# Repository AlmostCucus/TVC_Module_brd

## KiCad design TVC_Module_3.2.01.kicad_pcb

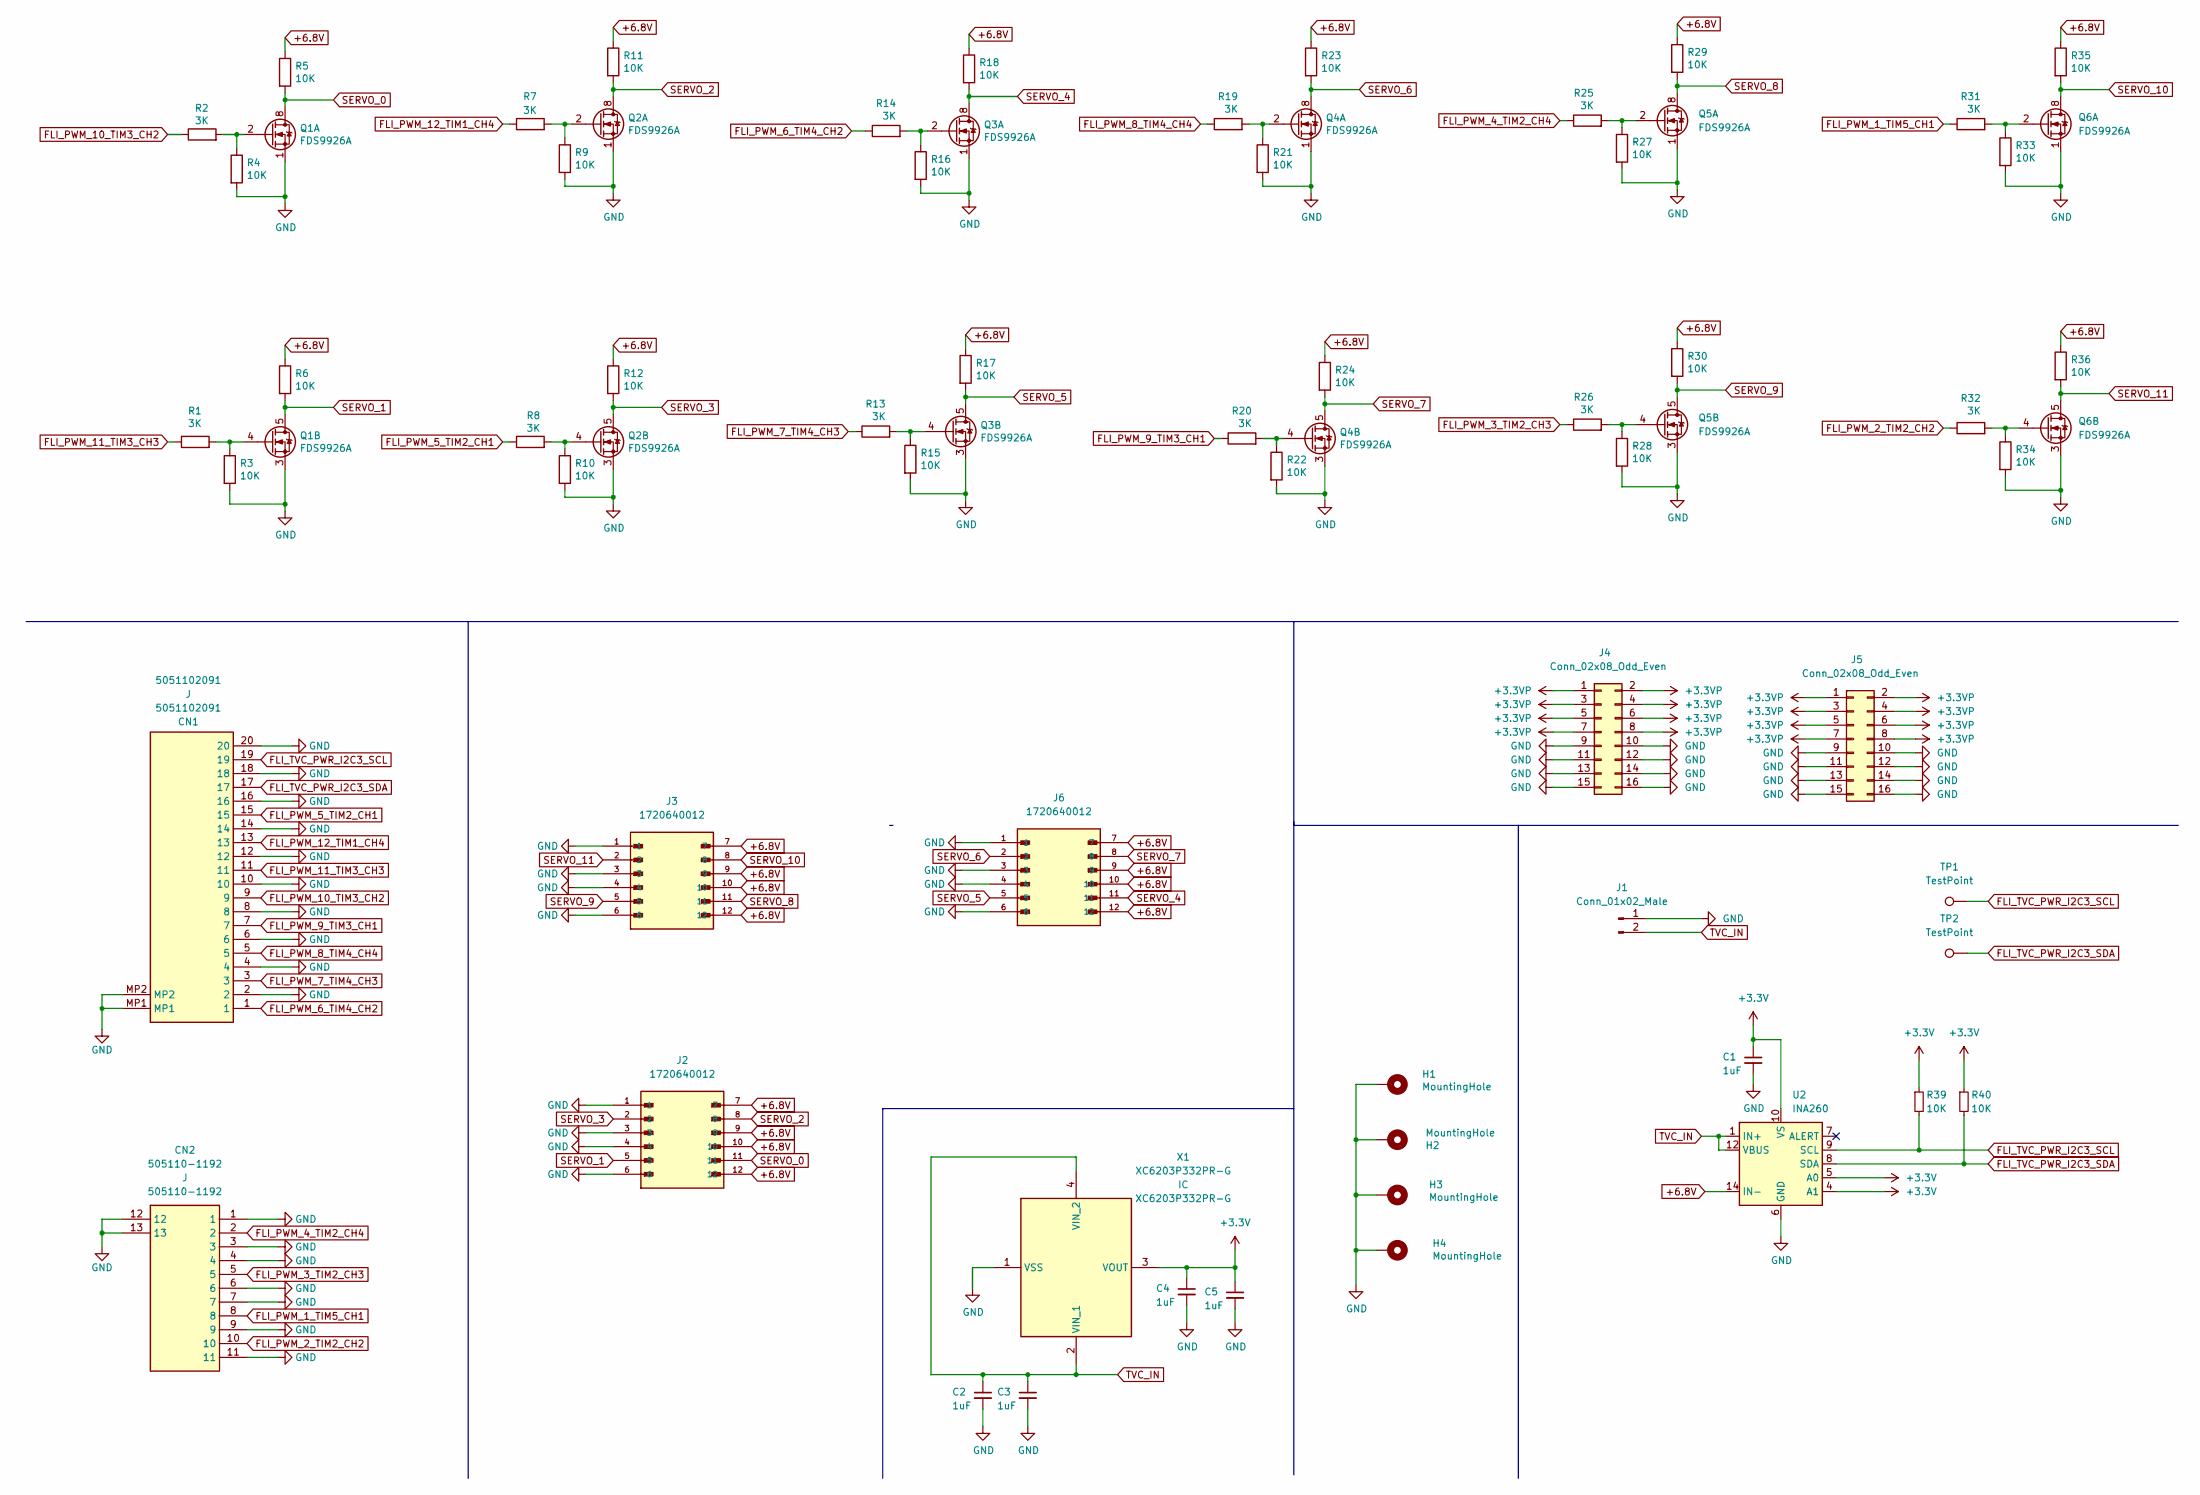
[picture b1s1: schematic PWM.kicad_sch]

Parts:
C1, C2, C3, C4, C5: 1uF; C_0402_1005Metric
CN1: 5051102091; Manufacturer_Part_Number 5051102091
CN2: 505110-1192; 5051101192; Manufacturer_Part_Number 505110-1192; Mouser Part Number 538-505110-1192
H1, H2, H3, H4: MountingHole; MountingHole_3.2mm_M3_Pad_Via
J1: Conn_01x02_Male; AMASS_XT30U-M_1x02_P5.0mm_Vertical
J2, J3, J6: 1720640012; MOLEX_1720640012; PARTREV E
J4: Conn_02x08_Odd_Even; PinHeader_2x08_P2.54mm_Vertical_SMD
J5: Conn_02x08_Odd_Even; PinSocket_2x08_P2.54mm_Vertical_SMD
Q1, Q2, Q3, Q4, Q5, Q6: FDS9926A; SOIC-8_3.9x4.9mm_P1.27mm
R1, R2, R7, R8, R13, R14, R19, R20, R25, R26, R31, R32: 3K; R_0402_1005Metric
R3, R4, R9, R10, R15, R16, R21, R22, R27, R28, R33, R34, R39, R40: 10K; R_0402_1005Metric
R5, R6, R11, R12, R17, R18, R23, R24, R29, R30, R35, R36: 10K; R_0805_2012Metric
TP1, TP2: TestPoint; TestPoint_Pad_D1.0mm
U2: INA260; TSSOP-16_4.4x5mm_P0.65mm
X1: XC6203P332PR-G; XC6203P332PRG; Manufacturer_Part_Number XC6203P332PR-G; Mouser Part Number 865-XC6203P332PR-G

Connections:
+3.3V: C1.1, C4.1, C5.1, R39.1, R40.1, U2.4 (A1), U2.5 (A0), U2.10 (VS), X1.3 (VOUT)
+3.3VP: J4.1, J4.2, J4.3, J4.4, J4.5, J4.6, J4.7, J4.8, J5.1, J5.2, J5.3, J5.4, J5.5, J5.6, J5.7, J5.8
+6.8V: J2.7, J2.9, J2.10, J2.12, J3.7, J3.9, J3.10, J3.12, J6.7, J6.9, J6.10, J6.12, R5.1, R6.1, R11.1, R12.1, R17.1, R18.1, R23.1, R24.1, R29.1, R30.1, R35.1, R36.1, U2.14 (IN-), U2.15 (IN-), U2.16 (IN-)
FLI_PWM_1_TIM5_CH1: CN2.8, R31.1
FLI_PWM_2_TIM2_CH2: CN2.10, R32.1
FLI_PWM_3_TIM2_CH3: CN2.5, R26.1
FLI_PWM_4_TIM2_CH4: CN2.2, R25.1
FLI_PWM_5_TIM2_CH1: CN1.15, R8.1
FLI_PWM_6_TIM4_CH2: CN1.1, R14.1
FLI_PWM_7_TIM4_CH3: CN1.3, R13.1
FLI_PWM_8_TIM4_CH4: CN1.5, R19.1
FLI_PWM_9_TIM3_CH1: CN1.7, R20.1
FLI_PWM_10_TIM3_CH2: CN1.9, R2.1
FLI_PWM_11_TIM3_CH3: CN1.11, R1.1
FLI_PWM_12_TIM1_CH4: CN1.13, R7.1
FLI_TVC_PWR_I2C3_SCL: CN1.19, R39.2, TP1.1, U2.9 (SCL)
FLI_TVC_PWR_I2C3_SDA: CN1.17, R40.2, TP2.1, U2.8 (SDA)
GND: C1.2, C2.2, C3.2, C4.2, C5.2, CN1.2, CN1.4, CN1.6, CN1.8, CN1.10, CN1.12, CN1.14, CN1.16, CN1.18, CN1.20, CN1.MP1, CN1.MP2, CN2.1, CN2.3, CN2.4, CN2.6, CN2.7, CN2.9, CN2.11, CN2.12, CN2.13, H1.1, H2.1, H3.1, H4.1, J1.1, J2.1, J2.3, J2.4, J2.6, J3.1, J3.3, J3.4, J3.6, J4.9, J4.10, J4.11, J4.12, J4.13, J4.14, J4.15, J4.16, J5.9, J5.10, J5.11, J5.12, J5.13, J5.14, J5.15, J5.16, J6.1, J6.3, J6.4, J6.6, Q1.1 (S1), Q1.3 (S2), Q2.1 (S1), Q2.3 (S2), Q3.1 (S1), Q3.3 (S2), Q4.1 (S1), Q4.3 (S2), Q5.1 (S1), Q5.3 (S2), Q6.1 (S1), Q6.3 (S2), R3.2, R4.2, R9.2, R10.2, R15.2, R16.2, R21.2, R22.2, R27.2, R28.2, R33.2, R34.2, U2.6 (GND), U2.11 (GND), X1.1 (VSS)
unnamed: Q1.2 (G1), R2.2, R4.1
unnamed: Q1.4 (G2), R1.2, R3.1
unnamed: Q2.2 (G1), R7.2, R9.1
unnamed: Q2.4 (G2), R8.2, R10.1
unnamed: Q3.2 (G1), R14.2, R16.1
unnamed: Q3.4 (G2), R13.2, R15.1
unnamed: Q4.2 (G1), R19.2, R21.1
unnamed: Q4.4 (G2), R20.2, R22.1
unnamed: Q5.2 (G1), R25.2, R27.1
unnamed: Q5.4 (G2), R26.2, R28.1
unnamed: Q6.2 (G1), R31.2, R33.1
unnamed: Q6.4 (G2), R32.2, R34.1
SERVO_0: J2.11, Q1.7 (D1), Q1.8 (D1), R5.2
SERVO_1: J2.5, Q1.5 (D2), Q1.6 (D2), R6.2
SERVO_2: J2.8, Q2.7 (D1), Q2.8 (D1), R11.2
SERVO_3: J2.2, Q2.5 (D2), Q2.6 (D2), R12.2
SERVO_4: J6.11, Q3.7 (D1), Q3.8 (D1), R18.2
SERVO_5: J6.5, Q3.5 (D2), Q3.6 (D2), R17.2
SERVO_6: J6.2, Q4.7 (D1), Q4.8 (D1), R23.2
SERVO_7: J6.8, Q4.5 (D2), Q4.6 (D2), R24.2
SERVO_8: J3.11, Q5.7 (D1), Q5.8 (D1), R29.2
SERVO_9: J3.5, Q5.5 (D2), Q5.6 (D2), R30.2
SERVO_10: J3.8, Q6.7 (D1), Q6.8 (D1), R35.2
SERVO_11: J3.2, Q6.5 (D2), Q6.6 (D2), R36.2
TVC_IN: C2.1, C3.1, J1.2, U2.1 (IN+), U2.2 (IN+), U2.3 (IN+), U2.12 (VBUS), X1.2 (VIN_1), X1.4 (VIN_2)

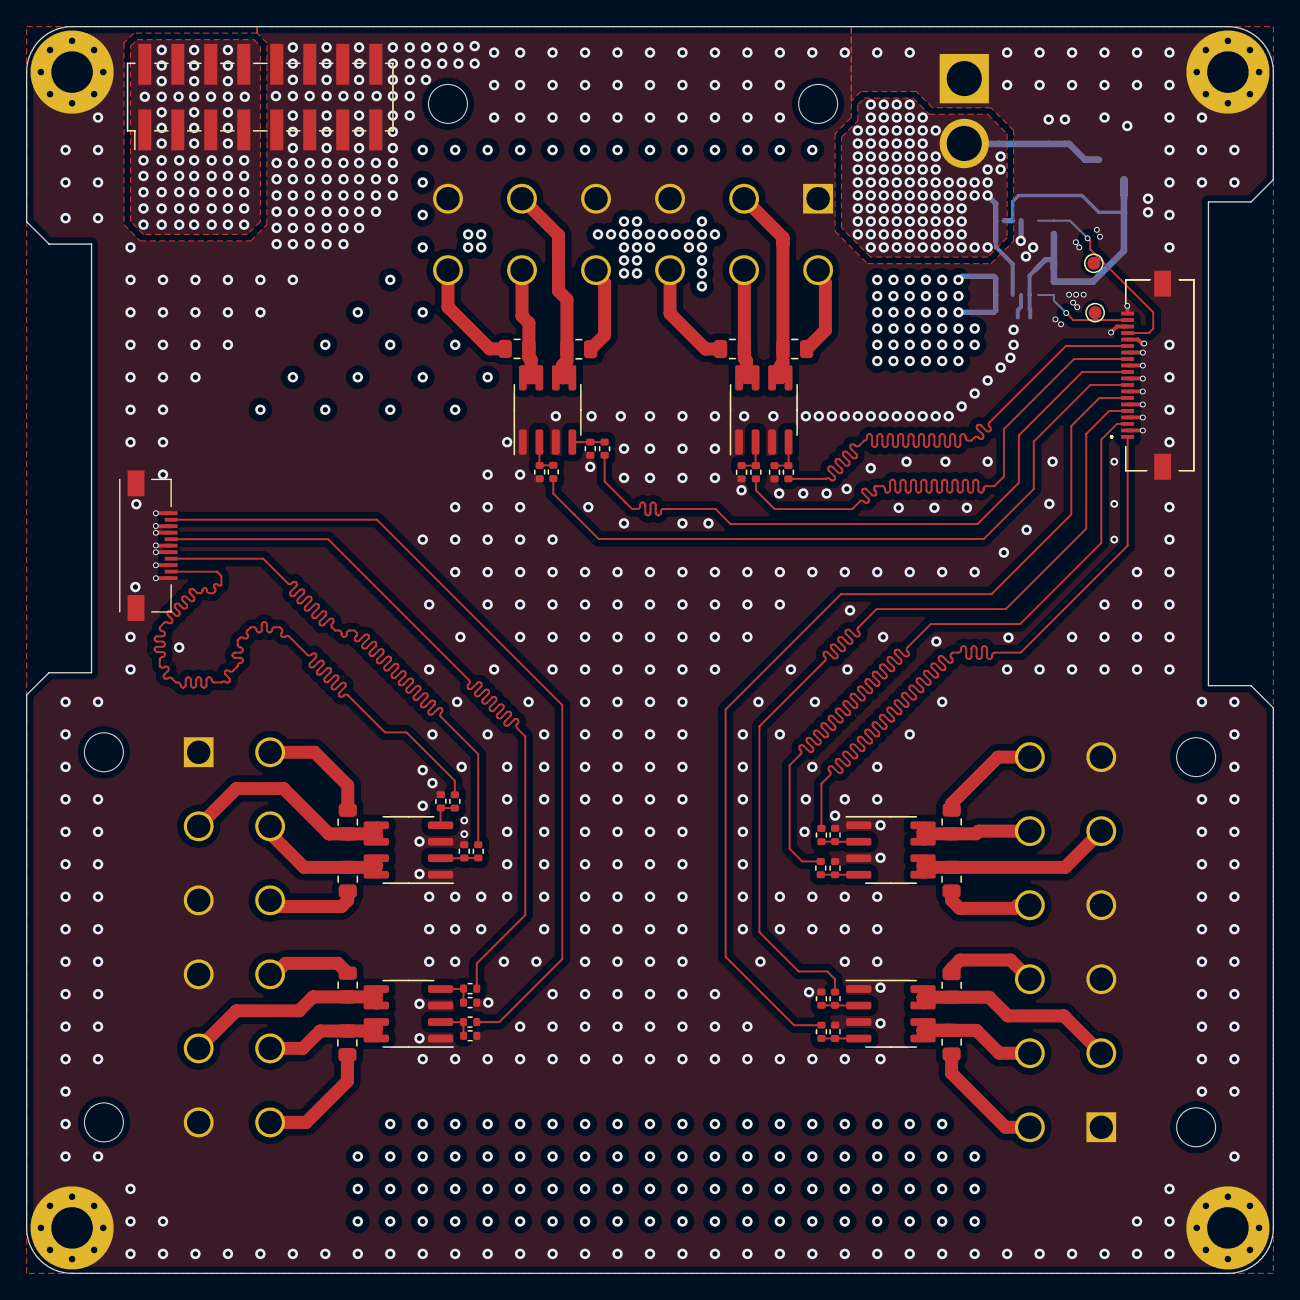
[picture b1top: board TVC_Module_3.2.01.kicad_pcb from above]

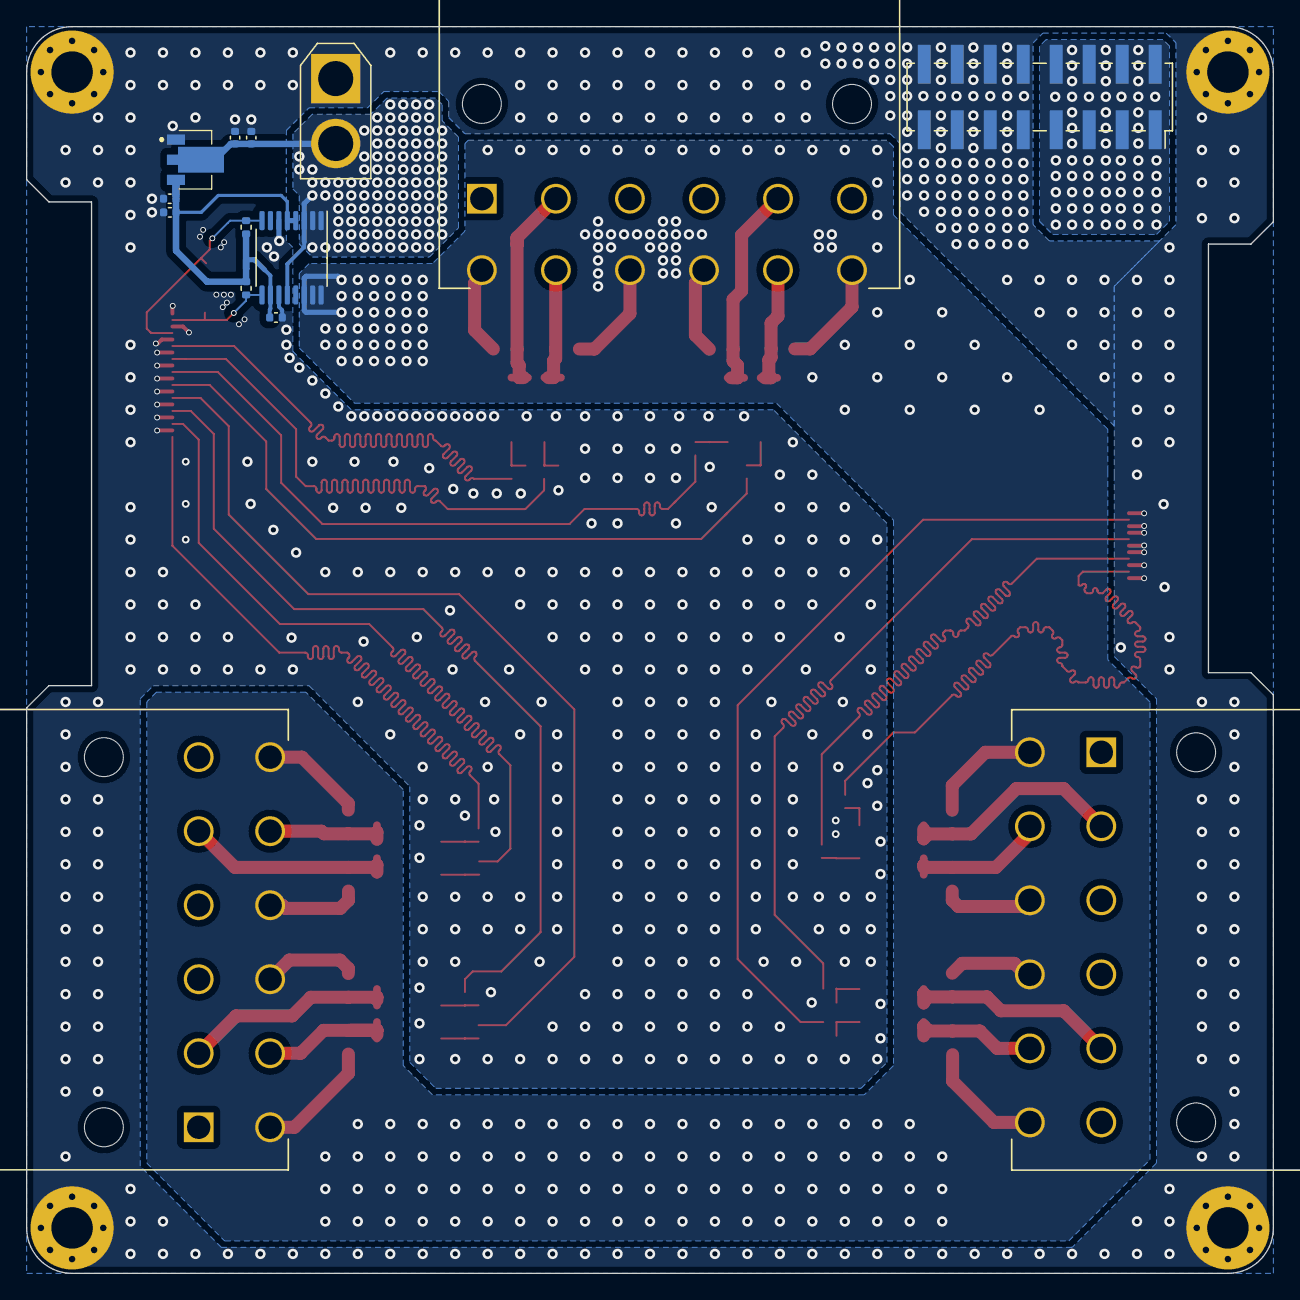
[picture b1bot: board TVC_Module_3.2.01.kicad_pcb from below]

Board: 4 copper layers, 96.0 x 96.0 mm, 65 parts (14 on the bottom side), 43 nets.

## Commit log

2025-06-20 I2C via position corrected
2025-06-20 Added GND vias
2025-06-20 Added more GND vias
2025-06-24 Changed PWR I2C address
2025-06-29 Corrected power planes
